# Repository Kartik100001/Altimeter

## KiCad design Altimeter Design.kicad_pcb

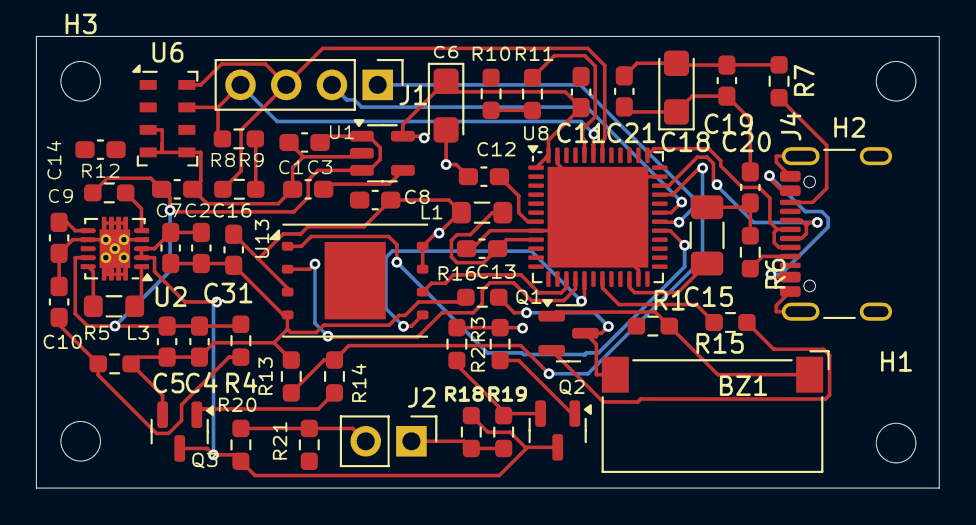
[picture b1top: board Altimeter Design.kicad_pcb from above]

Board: 4 copper layers, 50.2 x 25.1 mm, 59 parts (0 on the bottom side), 38 nets.

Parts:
BZ1: Buzzer; Speaker_CUI_CMR-1206S-67
C1: 105; C_0603_1608Metric_Pad1.08x0.95mm_HandSolder
C2, C7: 10uf; C_0603_1608Metric_Pad1.08x0.95mm_HandSolder
C3: 470pF; C_0603_1608Metric_Pad1.08x0.95mm_HandSolder
C4, C5, C16: 22uf; C_0603_1608Metric_Pad1.08x0.95mm_HandSolder
C6: 4.7uF; CP_EIA-3216-18_Kemet-A
C8, C11, C12, C13, C14, C19, C20, C21, C31: 104; C_0603_1608Metric_Pad1.08x0.95mm_HandSolder
C9: 0.1uf; C_0603_1608Metric_Pad1.08x0.95mm_HandSolder
C10: 10pf; C_0603_1608Metric_Pad1.08x0.95mm_HandSolder
C15: 4u7F; C_1206_3216Metric_Pad1.33x1.80mm_HandSolder
C18: 10uF; CP_EIA-3216-18_Kemet-A
H1, H2, H3, H4: M3; MountingHole_2.2mm_M2
J1: Conn_01x04; PinHeader_1x04_P2.54mm_Vertical
J2: Conn_01x02; PinHeader_1x02_P2.54mm_Vertical
J4: USB_C_Receptacle_USB2.0_16P; USB_C_Receptacle_GCT_USB4105-xx-A_16P_TopMnt_Horizontal
L1: 10uH; L_0805_2012Metric_Pad1.05x1.20mm_HandSolder
L3: 2.2uh; L_0805_2012Metric_Pad1.05x1.20mm_HandSolder
Q1: NPN; SOT-23
Q2, Q3: AO3400A; SOT-23
R1, R2, R14, R15: 1k; R_0603_1608Metric_Pad0.98x0.95mm_HandSolder
R3, R13: 470; R_0603_1608Metric_Pad0.98x0.95mm_HandSolder
R4: 1.2M; R_0603_1608Metric_Pad0.98x0.95mm_HandSolder
R5: 133K; R_0603_1608Metric_Pad0.98x0.95mm_HandSolder
R6, R7: 5.1k; R_0603_1608Metric_Pad0.98x0.95mm_HandSolder
R8, R9: 4K7; R_0603_1608Metric_Pad0.98x0.95mm_HandSolder
R10, R11: 10K; R_0603_1608Metric_Pad0.98x0.95mm_HandSolder
R12: 1M; R_0603_1608Metric_Pad0.98x0.95mm_HandSolder
R16, R18, R20: 330; R_0603_1608Metric_Pad0.98x0.95mm_HandSolder
R19, R21: 100; R_0603_1608Metric_Pad0.98x0.95mm_HandSolder
U1: MIC5219-3.3YM5; SOT-23-5
U2: TPS63060; Texas_S-PWSON-N10_ThermalVias
U6: MS5611-01BA; LGA-8_3x5mm_P1.25mm
U8: STM32F401CBU7; QFN-48-1EP_7x7mm_P0.5mm_EP5.6x5.6mm
U13: W25Q32JVZP; WSON-8-1EP_8x6mm_P1.27mm_EP3.4x4.3mm

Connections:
5VINP: J4.A4 (VBUS), J4.A9 (VBUS), J4.B4 (VBUS), J4.B9 (VBUS)
+3.3V: C6.1, C8.1, C11.1, C14.2, C18.1, C19.1, C20.1, C21.1, C31.2, L1.1, R1.1, R8.2, R9.2, U1.5 (OUT), U6.1 (VDD), U6.2 (PS), U8.1 (VBAT), U8.24 (VDD), U8.36 (VDD), U8.48 (VDD), U13.3 (IO2), U13.7 (IO3), U13.8 (VCC)
+5V: C1.2, C4.2, C5.2, C16.2, R4.1, R12.1, U1.1 (IN), U1.3 (EN), U2.9 (VOUT)
BOOT: R10.2, R11.1
GND: C1.1, C2.1, C3.2, C4.1, C5.1, C6.2, C7.1, C8.2, C9.2, C10.2, C11.2, C12.2, C13.2, C14.1, C15.2, C16.1, C18.2, C19.2, C20.2, C21.2, C31.1, J4.A1 (GND), J4.A12 (GND), J4.B1 (GND), J4.B12 (GND), J4.S1 (SHIELD), Q2.2 (S), Q3.2 (S), R3.1, R5.2, R6.1, R7.1, R10.1, R13.1, R16.1, R19.2, R21.2, U1.2 (GND), U2.4 (PS/SYNC), U2.7 (GND), U2.11 (PGND), U6.3 (GND), U6.4 (CSB), U6.5 (CSB), U8.8 (VSSA), U8.23 (VSS), U8.35 (VSS), U8.47 (VSS), U8.49 (VSS), U13.4 (GND)
I2C1-SCL: J1.3, R8.1, U6.8 (SCLK), U8.42 (PB6)
I2C1-SDA: J1.4, R9.1, U6.7 (SDI/SDA), U8.43 (PB7)
NRST: C12.1, U8.7 (NRST)
unnamed: BZ1.1 (+), Q1.1 (C), R1.2
unnamed: BZ1.2 (-), Q1.3 (E), R16.2
unnamed: J2.1, R18.1, R19.1
unnamed: J2.2, R20.1, R21.1
unnamed: J4.A5 (CC1), R6.2
unnamed: J4.B5 (CC2), R7.2
unnamed: Q1.2 (B), R15.2
unnamed: Q2.1 (G), R2.1
unnamed: Q3.1 (G), R14.1
unnamed: C3.1, U1.4 (BP)
unnamed: C10.1, R4.2, R5.1, U2.8 (FB)
unnamed: L3.1, U2.1 (L1)
unnamed: L3.2, U2.10 (L2)
unnamed: R12.2, U2.5 (PG)
unnamed: C9.1, U2.6 (VAUX)
unnamed: R11.2, U8.44 (BOOT0)
unnamed: R15.1, U8.19 (PB1)
unnamed: C15.1, U8.22 (VCAP1)
unnamed: C13.1, L1.2, U8.9 (VREF+)
PYRO1IP: R2.2, R3.2, U8.32 (PA11)
PYRO2IP: R13.2, R14.2, U8.33 (PA12)
RXD1: J1.2, U8.31 (PA10)
SPI1-MISO: U8.16 (PA6), U13.2 (DO(IO1))
SPI1-MOSI: U8.17 (PA7), U13.5 (DI(IO0))
SPI1-NSS2: U8.29 (PA8), U13.1 (~CS)
SPI1-SCK: U8.15 (PA5), U13.6 (CLK)
SWCLK: J4.A7 (D-), J4.B7 (D-), U8.37 (PA14)
SWDIO: J4.A6 (D+), J4.B6 (D+), U8.34 (PA13)
TXD1: J1.1, U8.30 (PA9)
VINP: C2.2, C7.2, Q2.3 (D), Q3.3 (D), R18.2, R20.2, U2.2 (VIN), U2.3 (EN)
